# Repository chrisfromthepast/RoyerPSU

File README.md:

View this project on [CADLAB.io](https://cadlab.io/project/24470). 

# RoyerPSU
tube mic power supply 100v and 6v for making mics based off of David Royer's design

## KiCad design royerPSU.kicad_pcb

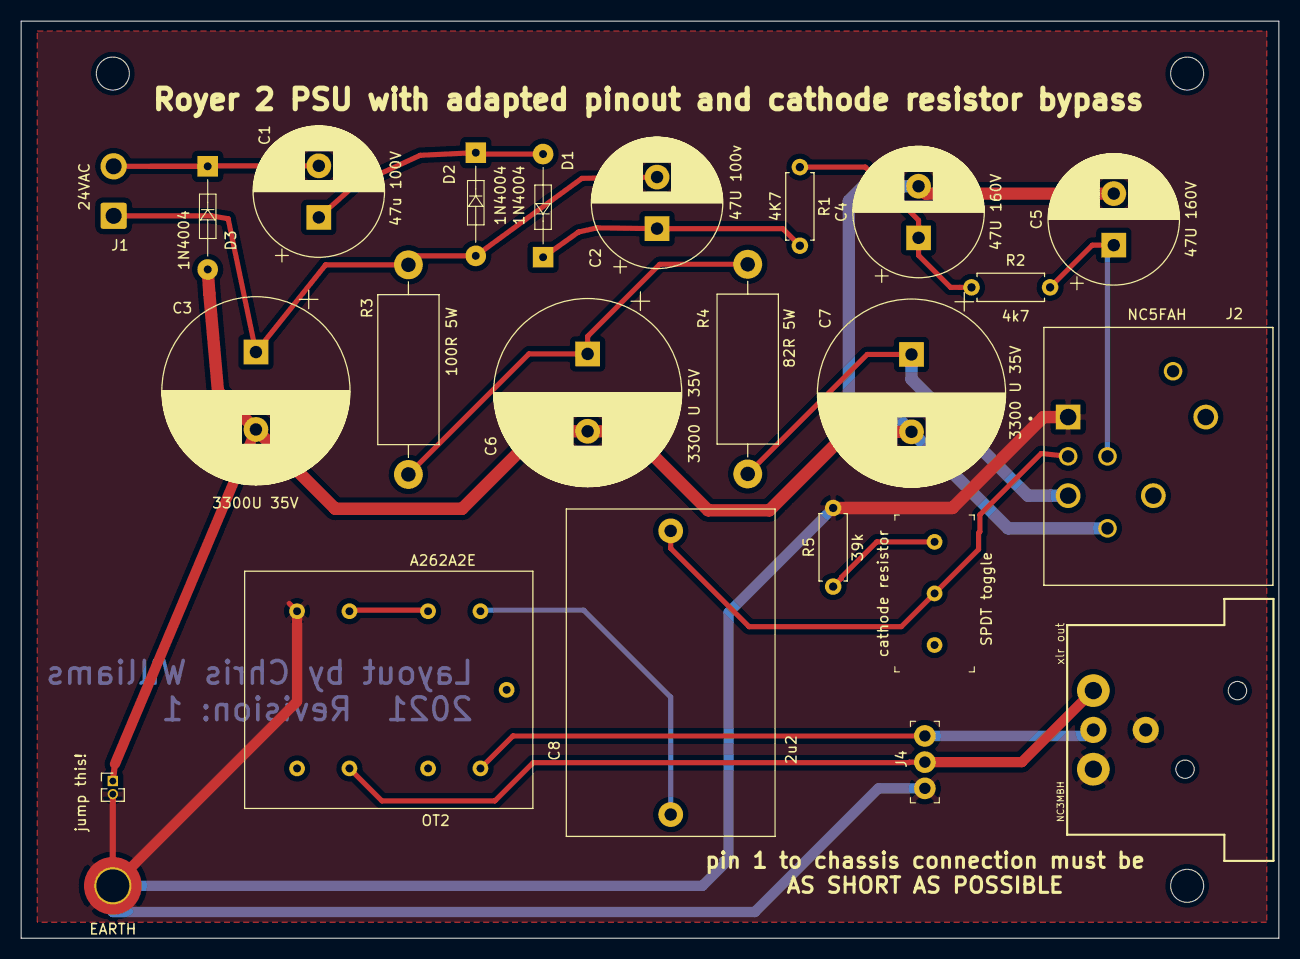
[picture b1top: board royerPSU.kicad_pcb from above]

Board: 2 copper layers, 121.9 x 88.9 mm, 27 parts (0 on the bottom side), 17 nets.

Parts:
 : MountingHole_3.2mm_M3
 #2,  #3: MountingHole_3.2mm_M3
C1: 47u 100V; CP_Radial_D12.5mm_P5.00mm
C2: 47U 100v; CP_Radial_D12.5mm_P5.00mm
C3: 3300U 35V; CP_Radial_D18.0mm_P7.50mm
C4, C5: 47U 160V; CP_Radial_D12.5mm_P5.00mm
C6, C7: 3300 U 35V; CP_Radial_D18.0mm_P7.50mm
C8: 2u2; C_Rect_L31.5mm_W20.0mm_P27.50mm_MKS4
D1, D2, D3: 1N4004; Diode_DO-35_P10mm
EARTH: MountingHole_3.2mm_M3_DIN965_Pad_TopBottom
J1: 24VAC; SolderWire-0.75sqmm_1x02_P4.8mm_D1.25mm_OD2.3mm
J2: NC5FAH; NEUTRIK_NC5FAH
J4: mic out; PinHeader_1x3_P2.54_Drill1.1mm
OT2: A262A2E; ae262a3E
R1: 4K7; R_Axial_DIN0207_L6.3mm_D2.5mm_P7.62mm_Horizontal
R2: 4k7; R_Axial_DIN0207_L6.3mm_D2.5mm_P7.62mm_Horizontal
R3: 100R 5W; R_Axial_DIN0614_L14.3mm_D5.7mm_P20.32mm_Horizontal
R4: 82R 5W; R_Axial_DIN0614_L14.3mm_D5.7mm_P20.32mm_Horizontal
R5: 39k; R_Axial_DIN0207_L6.3mm_D2.5mm_P7.62mm_Horizontal
cathode resistor: SPDT toggle; Term_Block_1x3_P5mm
jump this!: PinHeader_1x02_P1.27mm_Vertical
xlr out: NC3MBH

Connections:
+6V: C7.1, J2.5, R4.1
-BATT: C3.2, C4.2, C5.2, C6.2, C7.2, D3.2, J2.4, jump this!.1
Earth: EARTH.1, J2.1, J4.1, OT2.S2-, R5.2, jump this!.2, xlr out.1, xlr out.G
HT: C5.1, J2.2, R2.1
unnamed: C1.1, D1.2, D2.1
unnamed: C1.2, D3.1, J1.2
unnamed: C2.1, D1.1, R1.2
unnamed: C2.2, C3.1, D2.2, J1.1, R3.2
unnamed: C4.1, R1.1, R2.2
unnamed: C6.1, R3.1, R4.2
unnamed: C8.1, OT2.S1+
unnamed: J2.6, J2.7, J2.8
unnamed: J4.2, OT2.P1-, xlr out.2
unnamed: J4.3, OT2.P1+, xlr out.3
unnamed: OT2.S1-, OT2.S2+
unnamed: R5.1, cathode resistor.3
micSig: C8.2, J2.3, cathode resistor.2

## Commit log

2021-06-11 first commit, schematic is mostly done, footprints are mostly done, need to fininsh layout of output sections and guitar sections.
2021-06-12 mostly working layout of mic psu with cheapo output transformer still need chassis mounting and to choose 2 ground planes, and a way to link all the grunds toether at chassis complete this board as i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
2021-06-13 defined mounting holes, and 1 chassis mounting hole and star ground point removed all guitar related parts to create the royermod psu on its own need to define switch to toggle 39k cathode resistor
    exported gerbers for test build
    still need:
    front panel
    bom
    will define this as a release after double checking
2021-06-21 Backlink to CADLAB.io has been added.
2021-07-13 added some silk screen notes and makes small trace changes
2021-07-13 Delete royerPSU.sch
    this schematic was blank, find an older version
2021-07-13 Create RoyerPSU.sch
    went and found an old version
2021-07-13 added "power on" leds for voltage rails (to drain capacitors too)
2021-07-13 exported current gerbers
2021-07-13 zipped up the new gerbers
